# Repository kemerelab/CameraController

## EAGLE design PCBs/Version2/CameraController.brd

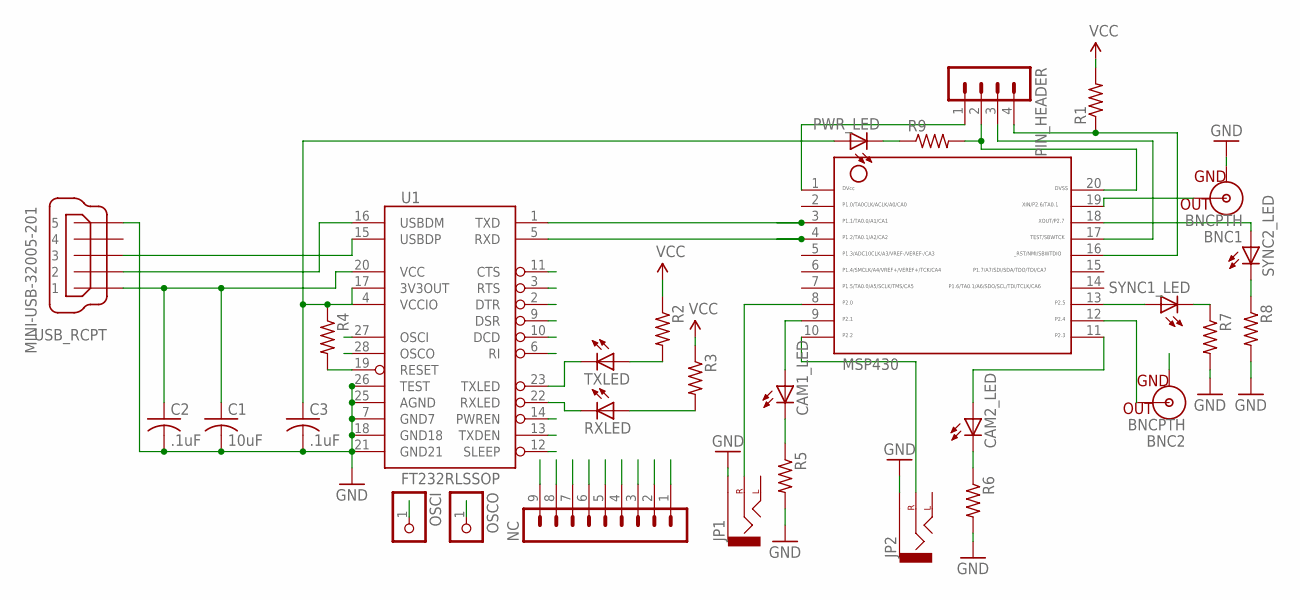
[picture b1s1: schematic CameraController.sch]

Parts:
BNC1, BNC2: BNCPTH; BNC
C1: 10uF; C0805
C2, C3: .1uF; C0603
CAM1_LED, CAM2_LED: LED_E; LED_1206
JP1, JP2: AUDIO-JACKPTH; AUDIO-JACK
MSP430: MSP430; 20_PIN
NC: MA09-1
OSCI: PINHD-1X1; 1X01
OSCO: PINHD-1X1; 1X01
PIN_HEADER: MA04-1
PWR_LED: LED_E; LED_1206
R1, R2, R3, R4, R5, R6, R7, R8, R9: R-US_R1206; R1206
RXLED: LED_E; LED_1206
SYNC1_LED, SYNC2_LED: LED_E; LED_1206
TXLED: LED_E; LED_1206
U1: FT232RLSSOP; SSOP28DB
USB_RCPT: MINI-USB-32005-201; 32005-201

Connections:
3V3: C3.1, MSP430.1, PIN_HEADER.1, PWR_LED.A, R4.1, U1.4 (VCCIO), U1.17 (3V3OUT)
CAM1: JP1.RING (RIGHT), MSP430.8
CAM1_LED: CAM1_LED.C, R5.1
CAM2: JP2.RING (RIGHT), MSP430.10
CTS: NC.4, U1.11 (CTS)
D+: U1.15 (USBDP), USB_RCPT.3
D-: U1.16 (USBDM), USB_RCPT.2
DCD: NC.5, U1.10 (DCD)
DSR: NC.6, U1.9 (DSR)
DTR: NC.9, U1.2 (DTR)
GND: BNC1.GND, BNC2.GND, C1.2, C2.2, C3.2, JP1.SLEEVE, JP2.SLEEVE, MSP430.20, PIN_HEADER.2, R5.2, R6.2, R7.2, R8.2, R9.2, U1.7 (GND7), U1.18 (GND18), U1.21 (GND21), U1.25 (AGND), U1.26 (TEST), USB_RCPT.5
LED1: CAM1_LED.A, MSP430.9
LED2: CAM2_LED.A, MSP430.11
unnamed: R2.2, TXLED.A
unnamed: RXLED.C, U1.22 (RXLED)
unnamed: R3.2, RXLED.A
unnamed: R4.2, U1.19 (RESET)
unnamed: CAM2_LED.C, R6.1
unnamed: MSP430.13, SYNC1_LED.A
unnamed: R7.1, SYNC1_LED.C
unnamed: MSP430.18, SYNC2_LED.A
unnamed: R8.1, SYNC2_LED.C
unnamed: PWR_LED.C, R9.1
unnamed: TXLED.C, U1.23 (TXLED)
OSCI: OSCI.1, U1.27 (OSCI)
OSCO: OSCO.1, U1.28 (OSCO)
PWREN: NC.1, U1.14 (PWREN)
RI: NC.7, U1.6 (RI)
RST: MSP430.16, PIN_HEADER.4, R1.1
RTS: NC.8, U1.3 (RTS)
RXD: MSP430.4, U1.5 (RXD)
SLEEP: NC.3, U1.12 (SLEEP)
SYNC1: BNC2.S (OUT), MSP430.12
SYNC2: BNC1.S (OUT), MSP430.19
TEST: MSP430.17, PIN_HEADER.3
TXD: MSP430.3, U1.1 (TXD)
TXDEN: NC.2, U1.13 (TXDEN)
VCC: C1.1, C2.1, R1.2, R2.1, R3.1, U1.20 (VCC), USB_RCPT.1

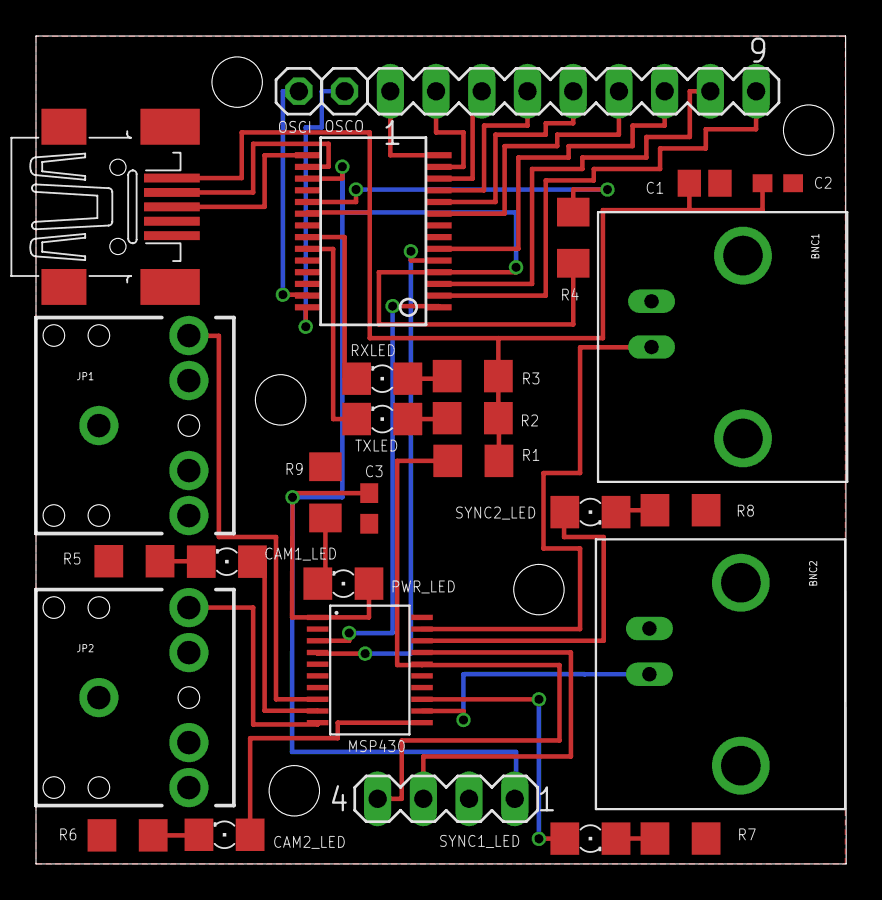
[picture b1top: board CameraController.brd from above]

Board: 2 copper layers, 45.0 x 46.0 mm, 30 parts (0 on the bottom side), 38 nets.

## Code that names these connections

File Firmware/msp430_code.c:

#include <msp430.h>
#include "stdint.h"


const unsigned long smclk_freq = 16000000;      // SMCLK frequency in hertz
const unsigned long bps = 9600;                 // Async serial bit rate
int freq = 30;									// Initial frequency when started up, can be changed using command-line interface
int i = 0;										//counter
int ALL = 0;								//flag for which "state" the controller is in
int SYNC1 = 0;
int SYNC2 = 0;
int CAM1 = 0;
int CAM2 = 0;
int SIDE1 = 0;
int SIDE2 = 0;
int SYNC = 0;
int CAM = 0;

char test[18];									//array for storing most recent input command

void out(data){                                 //function to output characters through the hardware uart
    while (!(IFG2 & UCA0TXIFG));
    UCA0TXBUF = data;
}

void pulse_delay(freq){							//return a delay of the width of one pulse, actual time depends on the current frequency
	if (freq == 30){
		_delay_cycles(16000000/60);
	}
	else if (freq == 60){
		_delay_cycles(16000000/120);
	}
	else if (freq == 40){
		_delay_cycles(16000000/80);
	}
	else if (freq == 50){
		_delay_cycles(16000000/100);
	}
	else if (freq == 15){
		_delay_cycles(16000000/30);
	}
}

void cameratest(void){					//test function. outputs 30 pulses
	for (i=30;i>0;i--){
		P2OUT ^= BIT0 + BIT1 + BIT2 + BIT3 + BIT4 + BIT5 + BIT6 + BIT7;
		pulse_delay(freq);

		P2OUT ^= BIT0 + BIT1 + BIT2 + BIT3 + BIT4 + BIT5 + BIT6 + BIT7;
		pulse_delay(freq);
	}
}

void main(void){
	WDTCTL = WDTPW + WDTHOLD;                 // Stop WDT
	BCSCTL1 = CALBC1_16MHZ;						//run the 16 MHz clock
	DCOCTL = CALDCO_16MHZ;
	P1SEL = BIT1 + BIT2 ;                     // P1.1 = RXD, P1.2=TXD
	P1SEL2 = BIT1 + BIT2 ;                     // P1.1 = RXD, P1.2=TXD, use for serial communication
	UCA0CTL1 |= UCSSEL_2;                     // SMCLK

	const unsigned long brd = (smclk_freq + (bps >> 1)) / bps; // Bit rate divisor

	UCA0BR1 = (brd >> 12) & 0xFF;               // High byte of whole divisor
	UCA0BR0 = (brd >> 4) & 0xFF;                // Low byte of whole divisor
	UCA0MCTL = ((brd << 4) & 0xF0) | UCOS16;    // Fractional divisor, oversampling mode

	UCA0CTL1 &= ~UCSWRST;                     // **Initialize USCI state machine**
	IE2 |= UCA0RXIE;                          // Enable USCI_A0 RX interrupt
	__bis_SR_register(GIE);
    P2SEL = 0;								// Select all the 2.X pins to general I/O
    P2SEL2 = 0;								// Select all the 2.X pins to general I/O

    P2DIR = BIT0 + BIT1 + BIT2 + BIT3 + BIT4 + BIT5 + BIT6 + BIT7; 		//Set all the 2.X pins to output
    P2OUT = BIT0 + BIT2 + BIT4 + BIT6;                                  //Initialize pins 2.0, 2.2, 2.4, and 2.6 to high

    while (1){								//main loop that will continuously output signal if a state is on

		while (ALL){						// output to all 2.X pins
				P2OUT ^= BIT0 + BIT1 + BIT2 + BIT3 + BIT4 + BIT5 + BIT6 + BIT7;
				pulse_delay(freq);
				P2OUT ^= BIT0 + BIT1 + BIT2 + BIT3 + BIT4 + BIT5 + BIT6 + BIT7;
				pulse_delay(freq);
			}

		while (SYNC1){						// output to BNC 1
				P2OUT ^= BIT4 + BIT5;
				pulse_delay(freq);
				P2OUT ^= BIT4 + BIT5;
				pulse_delay(freq);
			}


		while (SYNC2){						// output to BNC 2
				P2OUT ^= BIT6 + BIT7;
				pulse_delay(freq);
				P2OUT ^= BIT6 + BIT7;
				pulse_delay(freq);
			}


		while (CAM1){						// output to audio jack 1
				P2OUT ^= BIT0 + BIT1;
				pulse_delay(freq);
				P2OUT ^= BIT0 + BIT1;
				pulse_delay(freq);
			}

		while (CAM2){						// output to audio jack 2
				P2OUT ^= BIT2 + BIT3;
				pulse_delay(freq);
				P2OUT ^= BIT2 + BIT3;
				pulse_delay(freq);
			}

		while (SIDE1){						// output to 1 audio jack and 2 BNC
				P2OUT ^= BIT0 + BIT1 + BIT6 + BIT7;
				pulse_delay(freq);
				P2OUT ^= BIT0 + BIT1 + BIT6 + BIT7;
				pulse_delay(freq);
			}

		while (SIDE2){						// output to 1 audio jack and 1 BNC
				P2OUT ^= BIT2 + BIT3 + BIT4 + BIT5;
				pulse_delay(freq);
				P2OUT ^= BIT2 + BIT3 + BIT4 + BIT5;
				pulse_delay(freq);
			}

		while (SYNC){						// output to both BNC
				P2OUT ^= BIT4 + BIT5 + BIT6 + BIT7;
				pulse_delay(freq);
				P2OUT ^= BIT4 + BIT5 + BIT6 + BIT7;
				pulse_delay(freq);
			}

		while (CAM){						// output to both audio jacks
				P2OUT ^= BIT0 + BIT1 + BIT2 + BIT3;
				pulse_delay(freq);
				P2OUT ^= BIT0 + BIT1 + BIT2 + BIT3;
				pulse_delay(freq);
			}

    }

}

#pragma vector=USCIAB0RX_VECTOR
__interrupt void USCI0RX_ISR(void)
{

	 	out(UCA0RXBUF);             //return every character received

	    if (UCA0RXBUF == 0x0d){         //if enter is pressed, check to see if a valid command has been input
	        out('\r');					//return 'Enter'
	        out('\n');
			
			//change current frequency, keeps output state the same
	        if ((test[0] == 'z' || test[0] == 'Z') && (test[1] == 'h' || test[1] == 'H') && (test[2] == '0') && (test[3] == '3')){
	        	freq = 30;
	        }

	        else if ((test[0] == 'z' || test[0] == 'Z') && (test[1] == 'h' || test[1] == 'H') && (test[2] == '0') && (test[3] == '6')){
	        	freq = 60;
	        }

	        else if ((test[0] == 'z' || test[0] == 'Z') && (test[1] == 'h' || test[1] == 'H') && (test[2] == '0') && (test[3] == '4')){
	        	freq = 40;
	        }

	        else if ((test[0] == 'z' || test[0] == 'Z') && (test[1] == 'h' || test[1] == 'H') && (test[2] == '0') && (test[3] == '5')){
	        	freq = 50;
	        }

	        else if ((test[0] == 'z' || test[0] == 'Z') && (test[1] == 'h' || test[1] == 'H') && (test[2] == '5') && (test[3] == '1')){
	        	freq = 15;
	        }

	        else{
	        				ALL = SYNC1 = SYNC2 = CAM1 = CAM2 = SIDE1 = SIDE2 = SYNC = CAM = 0; // if any command other then changing frequency is pressed, clear all outputs before applying new output state

	        				if ((test[0] == 't'||test[0] == 'T') && (test[1] == 's' || test[1] == 'S') && (test[2] == 'e' || test[2] == 'E') && (test[3] == 't' || test[3] == 'T')){ //output test
	        		        	cameratest();
	        		        }
							
							//turn on an output state
	        				else if ((test[0] == 'l'||test[0] == 'L') && (test[1] == 'l' || test[1] == 'L') && (test[2] == 'a' || test[2] == 'A')){
	        		        	ALL ^= 1;
	        		        }

	        				else if ((test[0] == '1') && (test[1]=='c' || test[1]=='C') && (test[2] == 'n' || test[2] == 'N') && (test[3] == 'y' || test[3] == 'Y') && (test[4] == 's' || test[4] == 'S')){
	        		        	SYNC1 ^= 1;
	        		        }

	        				else if ((test[0] == '2') && (test[1]=='c' || test[1]=='C') && (test[2] == 'n' || test[2] == 'N') && (test[3] == 'y' || test[3] == 'Y') && (test[4] == 's' || test[4] == 'S')){
	        		        	SYNC2 ^= 1;
	        		        }

	        				else if ((test[0] == '1') && (test[1]=='m' || test[1]=='M') && (test[2] == 'a' || test[2] == 'A') && (test[3] == 'c' || test[3] == 'C')){
	        		        	CAM1 ^= 1;
	        		        }

	        				else if ((test[0] == '2') && (test[1]=='m' || test[1]=='M') && (test[2] == 'a' || test[2] == 'A') && (test[3] == 'c' || test[3] == 'C')){
	        		        	CAM2 ^= 1;
	        		        }

	        				else if ((test[0] == '1') && (test[1]=='E' || test[1]=='e') && (test[2] == 'd' || test[2] == 'D') && (test[3] == 'i' || test[3] == 'I') && (test[4] == 's' || test[4] == 'S')){
	        		        	SIDE1 ^= 1;
	        		        }

	        				else if ((test[0] == '2') && (test[1]=='E' || test[1]=='e') && (test[2] == 'd' || test[2] == 'D') && (test[3] == 'i' || test[3] == 'I') && (test[4] == 's' || test[4] == 'S')){
	        		        	SIDE2 ^= 1;
	        		        }

	        				else if ((test[0]=='c' || test[0]=='C') && (test[1] == 'n' || test[1] == 'N') && (test[2] == 'y' || test[2] == 'Y') && (test[3] == 's' || test[3] == 'S')){
	        		        	SYNC ^= 1;
	        		        }

	        				else if ((test[0]=='M' || test[0]=='m') && (test[1] == 'a' || test[1] == 'A') && (test[2] == 'c' || test[2] == 'C')){
	        		        	CAM ^= 1;
	        		        }
	        }


	    }
	    for (i = 17; i>0; i--){      //shift the array that stores the character inputs and input the new character at the bottom
	            test[i]=test[i-1];
		}
		test[0]=UCA0RXBUF;

}

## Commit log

2014-06-19 Initial commit. Directory structure. Initial Design.
2014-06-19 Added directories for documents and firmware
2014-06-19 Cleaned up gitignore and changed version name to 1.0
2014-06-20 Added values to CAM file. Changed fonts to vector, minimum size 25 mil, ratio 15%
2014-06-20 added manufacturing zip file
2014-07-07 Code for the MSP430
    Uploaded code for the MSP430 and a picture of the finished product
2014-07-07 Revert "Code for the MSP430"
    This reverts commit d3f698a71ac6643d06367277aa9b04a01f7f3e75.
2014-07-07 Finished Picture
2014-07-07 Small Update, Trivial
2014-07-07 Update README and MSP430 Code
2014-07-09 Update to README and MSP430 Code
2014-07-10 50 Hz Bug Fixed
2014-07-18 Camera Controller v2
    Moved mini USB and audio jacks closer to edge
    Added 5 mounting holes onto PCB
2014-08-20 Commented MSP430 Code
    Commented MSP430 code, mainly for Etienne

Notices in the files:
parts and their libraries:
SparkFun-DigitalIC: Licensing: CC v3.0 Share-Alike You are welcome to use this library for commercial purposes.
